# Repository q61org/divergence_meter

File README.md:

# Divergence Meter Project (by q61.org)

This is yet another divergence meter project.

This project tries to make a divergence meter that look just like the one in the Steins;Gate anime series, by implementing the following features:
- Using tip-less, flat-top nixie tubes (NL902) that look similar to the tubes in the anime.
- Compact dimensions: so that you can hold it on your hand like Suzuha does, and so that you can use the meter for cosplaying.
- A built-in, rechargeable battery; so that Suzuha can take it out of her bag while it is displaying a divergence value.

The result, a completed divergence meter can be seen below.

## Files in This Repository

This repository contains schematics, PCB files and a firmware of the divergence meter. Chassis design is left as an exercise to makers (forks and pull requests are welcome!).

The divergence meter is composed of 3 PCBs, and there are 3 PCB filesets in this repository:
- dm_control: A board that controls everything; the motherboard.
- dm_nixiebrd: A serial-to-parallel converter board with nixie drivers. This is the board where nixie tubes are mounted on, and stacks on top of dm_control board.
- dm_topboard: A perfboard-like board that goes on top of the divergence meter. This board does not have any electrical functions, but adds very much to the aesthetics.

dm_control board has a microcontroller, and its firmware is in the following subdirectory:
- dm_firmware: Firmware for dm_control board.

## License

Schematics and PCB, and firmware are licensed under different licenses:
- Schematics and PCB files are licensed under [Creative Commons BY-SA 4.0](https://creativecommons.org/licenses/by-sa/4.0/).
- Firmware is licensed under the BSD license. 

Please see README.md and LICENSE files in respective directories.

## See Also

This project was inspired by following projects:
- [Divergence Meter Project](http://www.mindspring.com/~tomtitor/)
- [世界线变动率探测仪 | Divergence Meter](http://www.nixieclock.org/?cat=219)

## Disclaimer

There is no warranty, expressed or implied, associated with files in this project. Especially there is a high voltage shock hazard which can kill you. Use at your own risk. 

## Author

Kouichi Kuroi (q61.org)
- Twitter: https://twitter.com/q61501331

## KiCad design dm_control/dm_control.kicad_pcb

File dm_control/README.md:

# dm_control Board

This board is the motherboard of the divergence meter.

The board has the following functionalities on board:
- Lithium-ion battery charger
- 3.7V to 180V DC/DC boost converter
- 3.7V to 3.3V DC/DC buck converter
- Microcontroller (ATmega328P) that controls nixie tubes
- USB to UART converter (FT231X)
- Accurate RTC (DS3234)

## About Power Supplies

You must be careful about power supplies on this board,
as they can be hazardous to you in some ways.

### Lithium-ion Battery Charger

This board has an MCP73831 battery charger chip. You can connect
a lithium-ion battery to connector P2 to make the divergence meter
free from power cords. 
However, you must be careful about what battery you use.

The MCP73831 chip controls only charging from the USB connector; 
it automatically stops charging when the battery is full, 
but it does not stop discharging when the battery is empty.

**There is no overdischarge protection on this board.**
Therefore you **MUST** use a battery with a built-in
overdischarge protection. **DO NOT USE RAW CELLS!**

Connector P2 is a 2-pin PH connector. This is a standard connector
for commonly available pouched LiPo cells. These batteries
usually have protection circuits, but double-check it before 
you actually use one.

### DC/DC Converters

This board has two DC/DC converters on board, a boost converter
that generates 180V for igniting nixie tubes, and a buck converter
that generates 3.3V for microcontroller and other digital chips.

The one that can harm you is, obviously, the boost converter.
Although it can only output some milliamps continuously, it has
2uF of smoothing capacitors (C14 and C15). 
When the converter is powered up without any load, it can charge 
the capacitors to their maximum capacity. This charge will remain 
in the capacitors after the converter is powered down, 
and when you touch them, all the charge can go through you.
This can be very bad.

When handling this board, always make sure that the power is off,
and that capacitors are discharged.

## Disclaimer (again)

There is no warranty, expressed or implied, associated with files in this project. Especially there is a high voltage shock hazard which can kill you. Use at your own risk. 

## License

Schematics and PCB files are licensed under Creative Commons BY-SA 4.0.

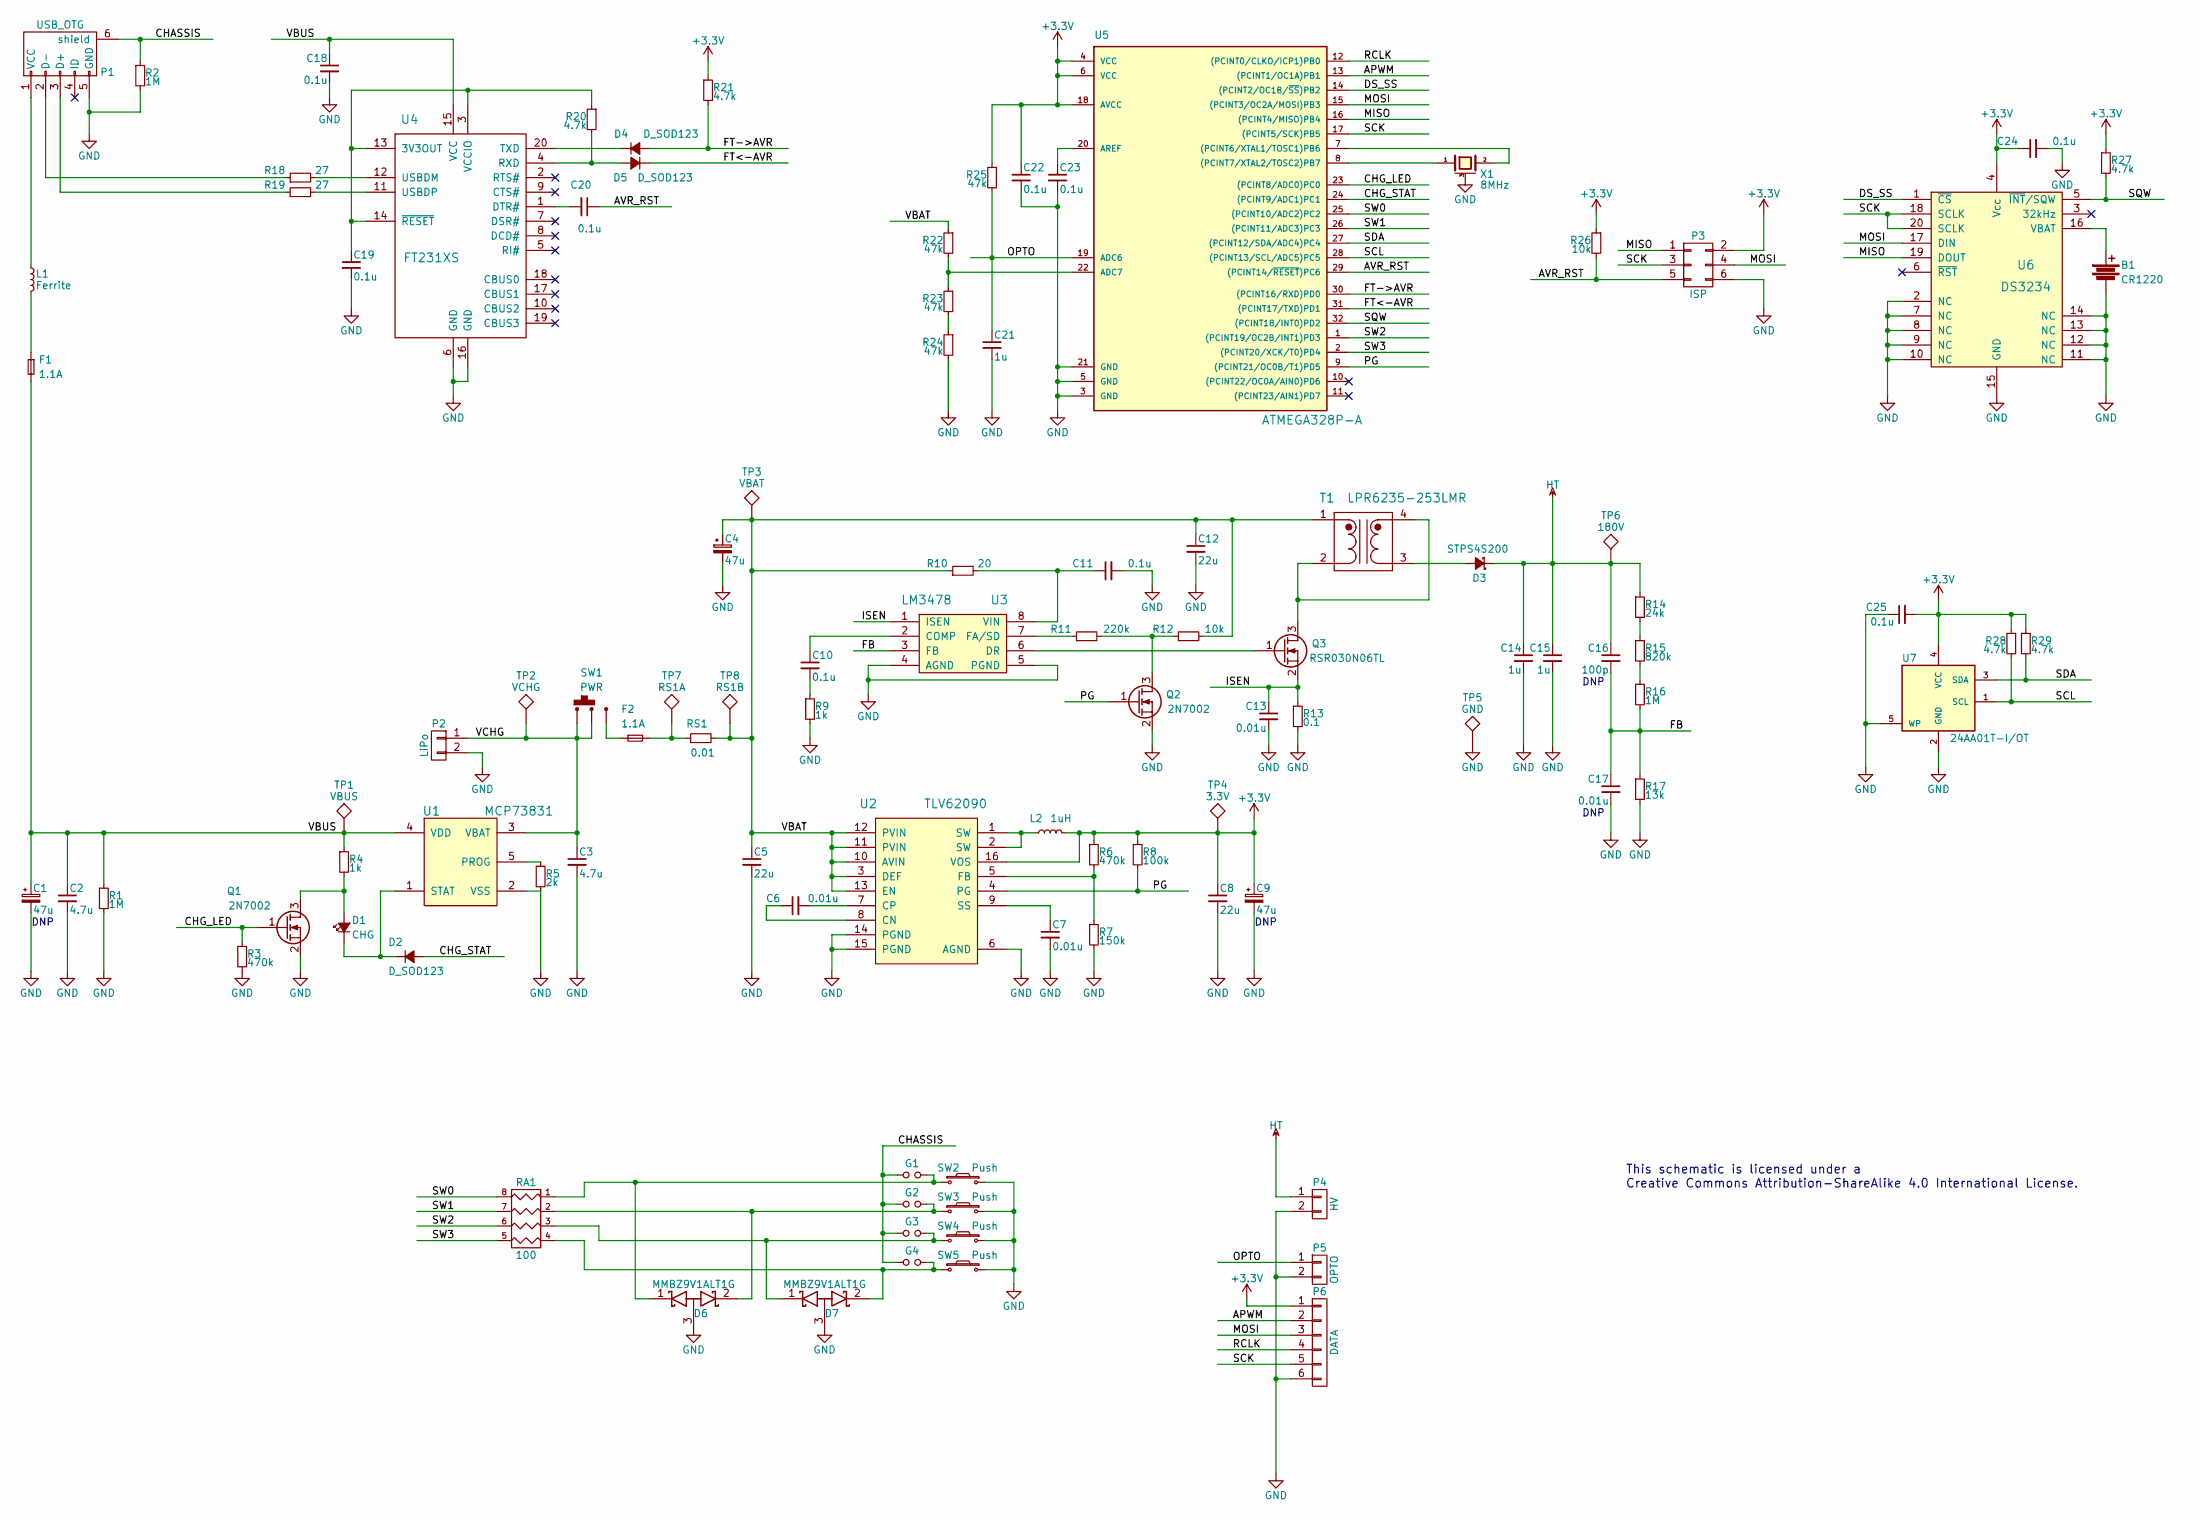
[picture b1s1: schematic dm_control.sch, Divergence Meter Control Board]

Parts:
B1: CR1220; Battery_CR1220
C1, C4, C9: 47u; C_Radial_D5_L6_P2.5
C2, C3: 4.7u; C_0805
C5, C8, C12: 22u; C_0805
C6, C7, C13, C17: 0.01u; C_0603
C10, C11, C18, C19, C20, C22, C23, C24, C25: 0.1u; C_0603
C14, C15: 1u; C_2220
C16: 100p; C_0805
C21: 1u; C_0603
D1: CHG; LED-3MM
D2, D4, D5: D_SOD123; SOD-123
D3: STPS4S200; SMB_Standard
D6, D7: MMBZ9V1ALT1G; SOT-23
F1, F2: 1.1A; R_1210
G1, G2, G3, G4: Jumper_NO_Small; SparkGap_0.2mm
L1: Ferrite; R_0805
L2: 1uH; Inductor_Taiyo-Yuden_NR-40xx
P1: USB_OTG; USB_Micro-B
P2: LiPo; Conn_S2B-PH-SM4-TB
P3: ISP; Pin_Header_Straight_2x03
P4: HV; Pin_Header_Straight_1x02
P5: OPTO; Pin_Header_Straight_1x02
P6: DATA; Pin_Header_Straight_1x06
Q1, Q2: 2N7002; SOT-23
Q3: RSR030N06TL; SOT-23
R1, R2, R16: 1M; R_0603
R3, R6: 470k; R_0603
R4, R9: 1k; R_0603
R5: 2k; R_0603
R7: 150k; R_0603
R8: 100k; R_0603
R10: 20; R_0603
R11: 220k; R_0603
R12, R26: 10k; R_0603
R13: 0.1; R_1206
R14: 24k; R_0603
R15: 820k; R_0603
R17: 13k; R_0603
R18, R19: 27; R_0603
R20, R21, R27, R28, R29: 4.7k; R_0603
R22, R23, R24, R25: 47k; R_0603
RA1: 100; R_Array_Convex_4x0603
RS1: 0.01; R_0603
SW1: PWR; PINHEAD1-3
SW2, SW3, SW4, SW5: Push; SW_Tactile_SPST_Angled
T1: LPR6235-253LMR; Transformer_CTX02-18714-R
TP1: VBUS; Pin_Header_Straight_1x01
TP2: VCHG; Pin_Header_Straight_1x01
TP3: VBAT; Pin_Header_Straight_1x01
TP4: 3.3V; Pin_Header_Straight_1x01
TP5: GND; Pin_Header_Straight_1x01
TP6: 180V; Pin_Header_Straight_1x01
TP7: RS1A; Pin_Header_Straight_1x01
TP8: RS1B; Pin_Header_Straight_1x01
U1: MCP73831; SOT-23-5
U2: TLV62090; QFN-16-1EP_3x3mm_Pitch0.5mm
U3: LM3478; MSOP-8_3x3mm_Pitch0.65mm
U4: FT231XS; SSOP-20_4.0x8.5mm_Pitch0.635mm
U5: ATMEGA328P-A; TQFP-32_7x7mm_Pitch0.8mm
U6: DS3234; SOIC-20W_7.5x12.8mm_Pitch1.27mm
U7: 24AA01T-I/OT; SOT-23-5
X1: 8MHz; Ceralock_CSTCE-G

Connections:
+3V3: C8.1, C9.1, C22.1, C24.1, C25.2, L2.2, P3.2, P6.1, R6.1, R8.1, R21.1, R25.1, R26.1, R27.1, R28.1, R29.1, TP4.1, U2.16 (VOS), U5.4 (VCC), U5.6 (VCC), U5.18 (AVCC), U6.4 (Vcc), U7.4 (VCC)
/APWM: P6.2, U5.13 ((PCINT1/OC1A)PB1)
/AVR_RST: C20.1, P3.5, R26.2, U5.29 ((PCINT14/~RESET~)PC6)
/CHASSIS: G1.2, G2.2, G3.2, G4.2, P1.6 (shield), R2.1, SW1.4, SW2.3, SW2.4, SW3.3, SW3.4, SW4.3, SW4.4, SW5.3, SW5.4
/CHG_LED: Q1.1 (G), R3.1, U5.23 ((PCINT8/ADC0)PC0)
/CHG_STAT: D2.2 (A), U5.24 ((PCINT9/ADC1)PC1)
/DS_SS: U5.14 ((PCINT2/OC1B/~SS~)PB2), U6.1 (~CS)
/FB: C16.2, C17.1, R16.2, R17.1, U3.3 (FB)
/FT->AVR: D4.2 (A), R21.2, U5.30 ((PCINT16/RXD)PD0)
/FT<-AVR: D5.1 (K), U5.31 ((PCINT17/TXD)PD1)
/ISEN: C13.1, Q3.2 (S), R13.1, U3.1 (ISEN)
/MISO: P3.1, U5.16 ((PCINT4/MISO)PB4), U6.19 (DOUT)
/MOSI: P3.4, P6.3, U5.15 ((PCINT3/OC2A/MOSI)PB3), U6.17 (DIN)
/OPTO: C21.1, P5.1, R25.2, U5.19 (ADC6)
/PG: Q2.1 (G), R8.2, U2.4 (PG), U5.9 ((PCINT21/OC0B/T1)PD5)
/RCLK: P6.4, U5.12 ((PCINT0/CLKO/ICP1)PB0)
/SCK: P3.3, P6.5, U5.17 ((PCINT5/SCK)PB5), U6.18 (SCLK), U6.20 (SCLK)
/SCL: R28.2, U5.28 ((PCINT13/SCL/ADC5)PC5), U7.1 (SCL)
/SDA: R29.2, U5.27 ((PCINT12/SDA/ADC4)PC4), U7.3 (SDA)
/SQW: R27.2, U5.32 ((PCINT18/INT0)PD2), U6.5 (~INT~/SQW)
/SW0: RA1.8 (R1), U5.25 ((PCINT10/ADC2)PC2)
/SW1: RA1.7 (R2), U5.26 ((PCINT11/ADC3)PC3)
/SW2: RA1.6 (R3), U5.1 ((PCINT19/OC2B/INT1)PD3)
/SW3: RA1.5 (R4), U5.2 ((PCINT20/XCK/T0)PD4)
/VBAT: C4.1, C5.1, C12.1, R10.1, R12.2, R22.1, RS1.2, T1.1, TP3.1, TP8.1, U2.3 (DEF), U2.10 (AVIN), U2.11 (PVIN), U2.12 (PVIN), U2.13 (EN)
/VBUS: C1.1, C2.1, C18.1, F1.2, R1.1, R4.1, TP1.1, U1.4 (VDD), U4.15 (VCC)
/VCHG: C3.1, P2.1, SW1.1, SW1.2, TP2.1, U1.3 (VBAT)
GND: B1.2, C1.2, C2.2, C3.2, C4.2, C5.2, C7.2, C8.2, C9.2, C11.2, C12.2, C13.2, C14.2, C15.2, C17.2, C18.2, C19.2, C21.2, C22.2, C23.2, C24.2, C25.1, D6.3 (A), D7.3 (A), P1.5 (GND), P2.2, P3.6, P4.2, P5.2, P6.6, Q1.2 (S), Q2.2 (S), R1.2, R2.2, R3.2, R5.2, R7.2, R9.2, R13.2, R17.2, R24.2, SW2.2, SW3.2, SW4.1, SW5.1, TP5.1, U1.2 (VSS), U2.6 (AGND), U2.14 (PGND), U2.15 (PGND), U3.4 (AGND), U3.5 (PGND), U4.6 (GND), U4.16 (GND), U5.3 (GND), U5.5 (GND), U5.21 (GND), U6.2 (NC), U6.7 (NC), U6.8 (NC), U6.9 (NC), U6.10 (NC), U6.11 (NC), U6.12 (NC), U6.13 (NC), U6.14 (NC), U6.15 (GND), U7.2 (GND), U7.5 (WP), X1.3 (case)
HT: C14.1, C15.1, C16.1, D3.1 (K), P4.1, R14.1, TP6.1
unnamed: B1.1, U6.16 (VBAT)
unnamed: C6.1, U2.8 (CN)
unnamed: C6.2, U2.7 (CP)
unnamed: C7.1, U2.9 (SS)
unnamed: C10.1, U3.2 (COMP)
unnamed: C10.2, R9.1
unnamed: C11.1, R10.2, U3.8 (VIN)
unnamed: C19.1, R20.1, U4.3 (VCCIO), U4.13 (3V3OUT), U4.14 (~RESET)
unnamed: C20.2, U4.1 (DTR#)
unnamed: C23.1, U5.20 (AREF)
unnamed: D1.1 (K), D2.1 (K), U1.1 (STAT)
unnamed: D1.2 (A), Q1.3 (D), R4.2
unnamed: D3.2 (A), T1.3
unnamed: D4.1 (K), U4.20 (TXD)
unnamed: D5.2 (A), R20.2, U4.4 (RXD)
unnamed: D6.1 (K), G1.1, RA1.1, SW2.1
unnamed: D6.2 (K), G2.1, RA1.2, SW3.1
unnamed: D7.1 (K), G3.1, RA1.3, SW4.2
unnamed: D7.2 (K), G4.1, RA1.4, SW5.2
unnamed: F1.1, L1.2
unnamed: F2.1, SW1.3
unnamed: F2.2, RS1.1, TP7.1
unnamed: L1.1, P1.1 (VCC)
unnamed: L2.1, U2.1 (SW), U2.2 (SW)
unnamed: P1.2 (D-), R18.1
unnamed: P1.3 (D+), R19.1
unnamed: Q2.3 (D), R11.2, R12.1
unnamed: Q3.1 (G), U3.6 (DR)
unnamed: Q3.3 (D), T1.2, T1.4
unnamed: R5.1, U1.5 (PROG)
unnamed: R6.2, R7.1, U2.5 (FB)
unnamed: R11.1, U3.7 (FA/SD)
unnamed: R14.2, R15.1
unnamed: R15.2, R16.1
unnamed: R18.2, U4.12 (USBDM)
unnamed: R19.2, U4.11 (USBDP)
unnamed: R22.2, R23.1, U5.22 (ADC7)
unnamed: R23.2, R24.1
unnamed: U5.7 ((PCINT6/XTAL1/TOSC1)PB6), X1.2
unnamed: U5.8 ((PCINT7/XTAL2/TOSC2)PB7), X1.1

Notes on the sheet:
This schematic is licensed under a Creative Commons Attribution-ShareAlike 4.0 International License.
DNP

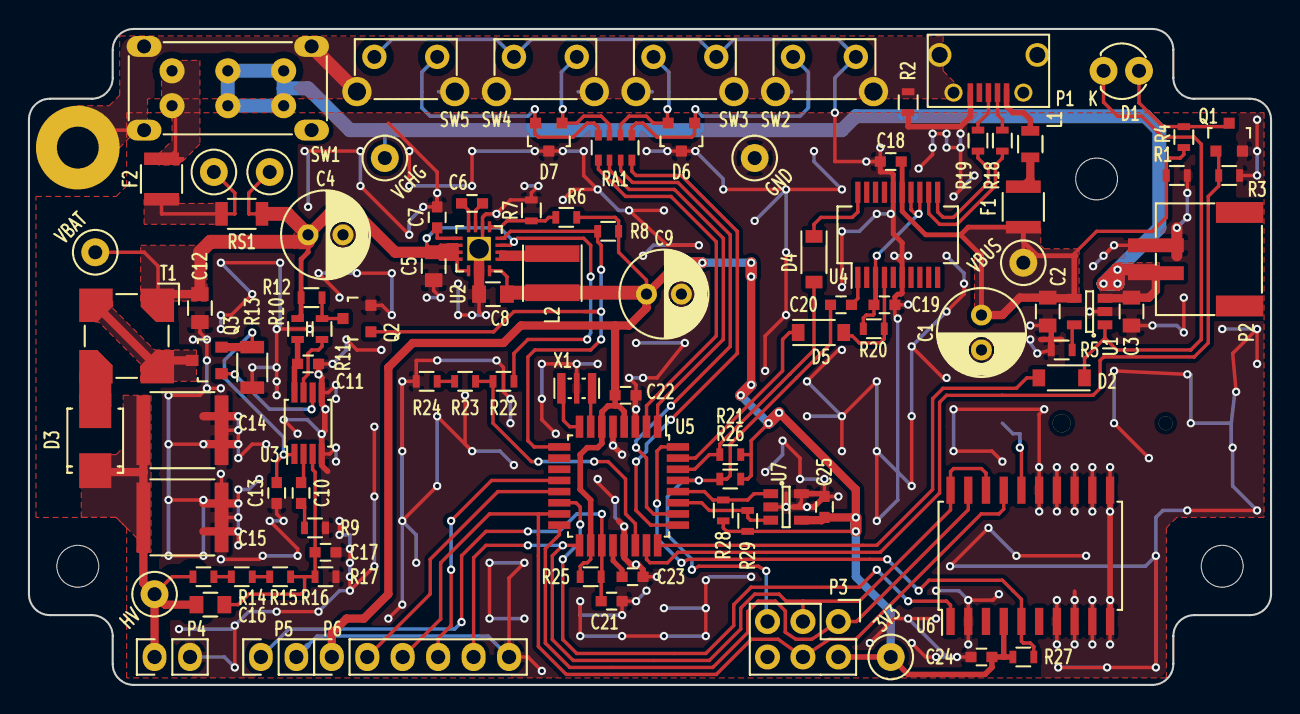
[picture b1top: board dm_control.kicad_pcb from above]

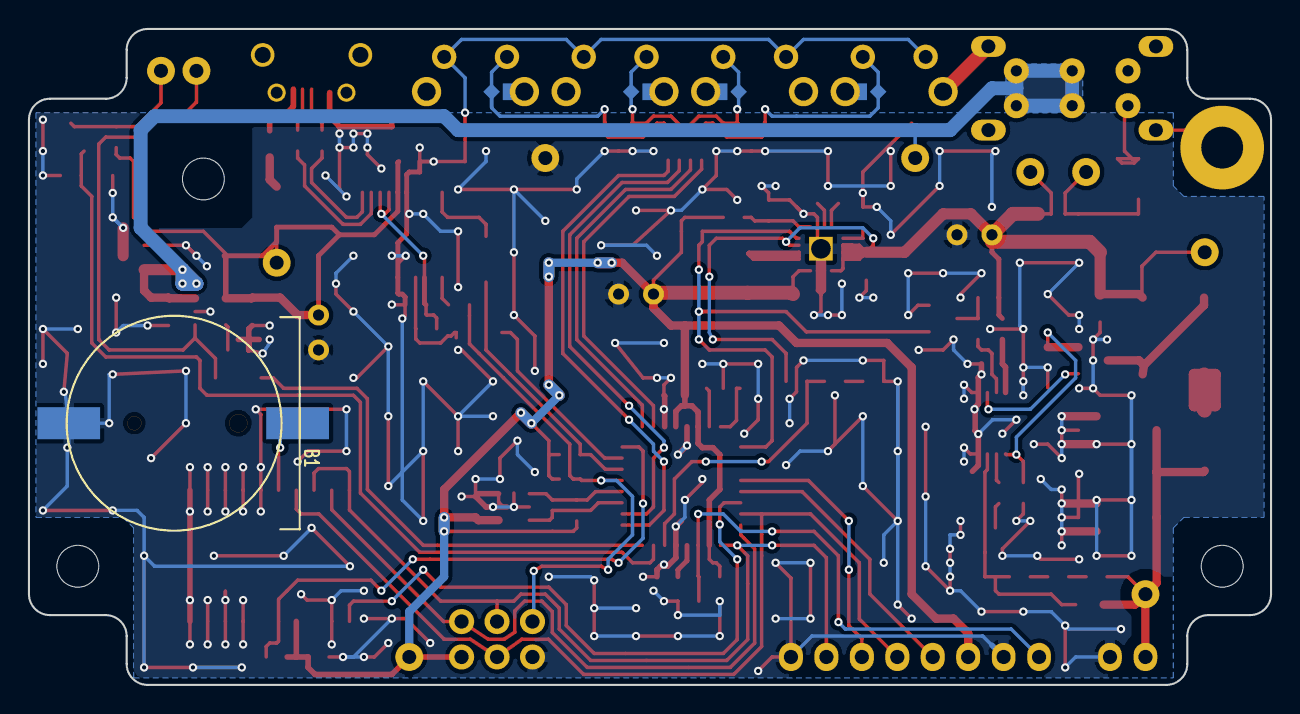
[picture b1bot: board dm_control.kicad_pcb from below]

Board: 2 copper layers, 89.0 x 47.0 mm, 103 parts (5 on the bottom side), 69 nets.

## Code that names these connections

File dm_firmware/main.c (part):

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

// ======== PORT MAPPING ========
// PB0 -> 595 LATCH CLK
// PB1 -> (PWM) Optocoupler Cathodes
// PB2 -> RTC Chip Select
// PB3 -> (SPI) MOSI
// PB4 <- (SPI) MISO
// PB5 -> (SPI) SCK
// PC0 -> Charge LED Inhibit
// PC1 <- Charge Status (PU)
// PC2 <- Switch 1 (PU)
// PC3 <- Switch 2 (PU)
// PC4 <> (I2C) SDA
// PC5 <> (I2C) SCL
// PD0 <- (UART) RxD
// PD1 -> (UART) TxD
// PD2 <- RTC SQW
// PD3 <- Switch 3 (PU)
// PD4 <- Switch 4 (PU)
// PD5 <- Power Good
// PD6    NC
// PD7    NC
// ADC6 <- Opto Transistor
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
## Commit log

2017-04-22 adding all the files
2017-04-27 fixed markdown formats
2017-04-27 adjust markdown formatting
2017-04-27 adjusted license section

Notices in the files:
dm_firmware/main.c:
Copyright (c) 2017, Kouichi Kuroi (q61.org)
All rights reserved.
dm_control/dm_control.kicad_pcb:
License: CC BY-SA 4.0 International
This PCB file is licensed under a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
